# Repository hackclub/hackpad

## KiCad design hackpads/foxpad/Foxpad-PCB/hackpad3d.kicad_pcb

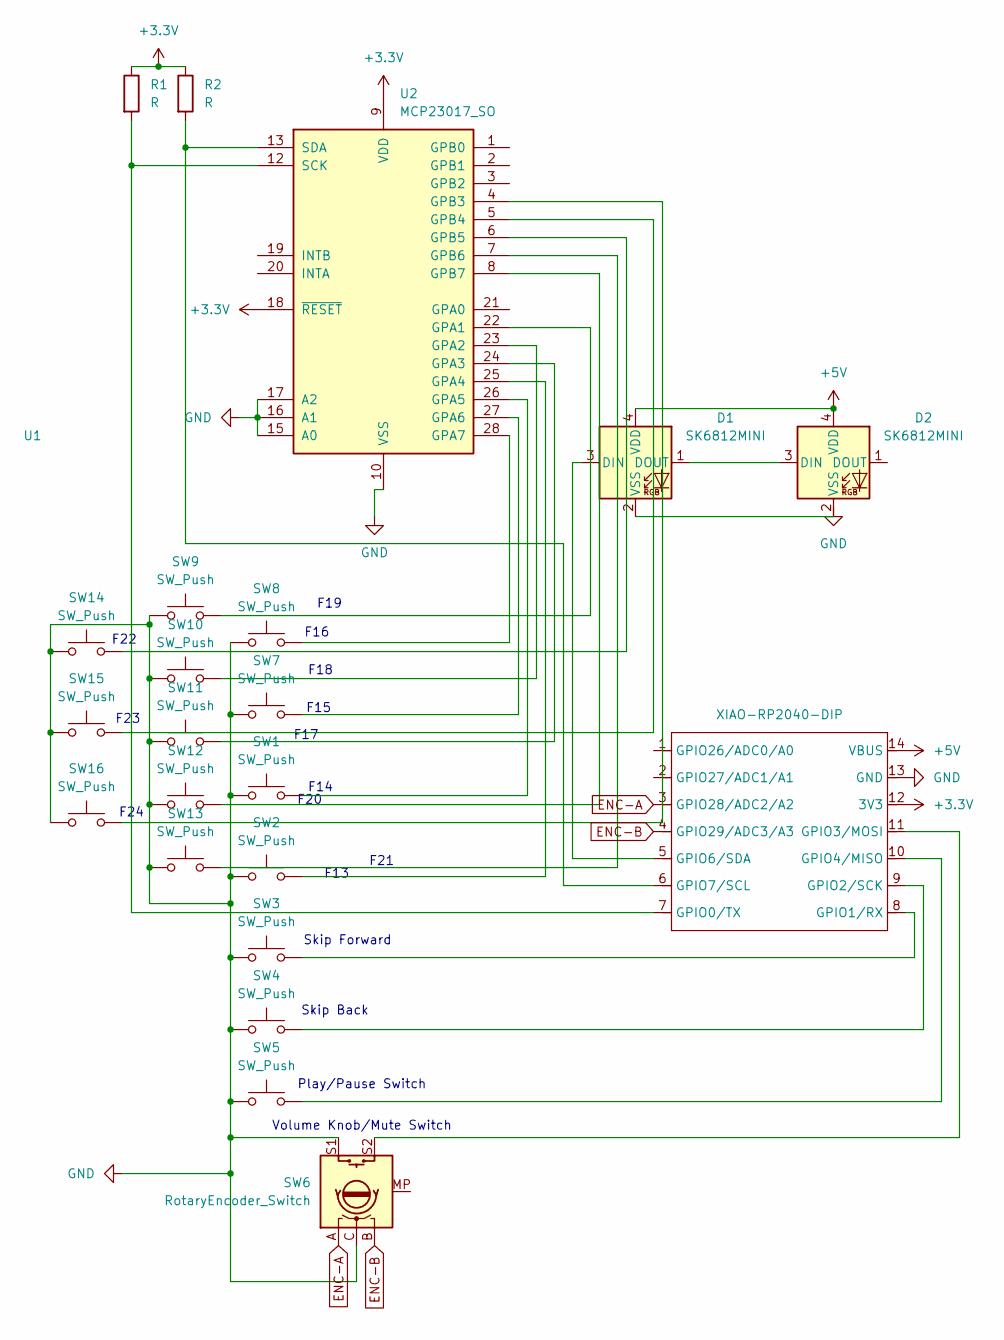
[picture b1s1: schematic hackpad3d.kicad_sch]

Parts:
D1, D2: SK6812MINI; LED_SK6812MINI_PLCC4_3.5x3.5mm_P1.75mm_3D
R1, R2: R; R_Axial_DIN0204_L3.6mm_D1.6mm_P7.62mm_Horizontal
SW1, SW2, SW3, SW4, SW5, SW7, SW8, SW9, SW10, SW11, SW12, SW13, SW14, SW15, SW16: SW_Push; SW_Cherry_MX_1.00u_PCB_3D
SW6: RotaryEncoder_Switch; RotaryEncoder_Alps_EC11E-Switch_Vertical_H20mm_CircularMoun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
U1: XIAO-RP2040-DIP; XIAO-RP2040-DIP-3D
U2: MCP23017_SO; SOIC-28W_7.5x17.9mm_P1.27mm

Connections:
+3.3V: R1.1, R2.1, U1.12 (3V3), U2.9 (VDD), U2.18 (~RESET)
+5V: D1.4 (VDD), D2.4 (VDD), U1.14 (VBUS)
ENC-A: SW6.A, U1.3 (GPIO28/ADC2/A2)
ENC-B: SW6.B, U1.4 (GPIO29/ADC3/A3)
GND: SW1.1, SW2.1, SW3.1, SW4.1, SW5.1, SW6.C, SW6.S1, SW7.1, SW8.1, SW9.1, SW10.1, SW11.1, SW12.1, SW13.1, SW14.1, SW15.1, SW16.1, U1.13 (GND), U2.10 (VSS), U2.15 (A0), U2.16 (A1), U2.17 (A2)
unnamed: D1.3 (DIN), U1.5 (GPIO6/SDA)
unnamed: D1.1 (DOUT), D2.3 (DIN)
unnamed: D1.2 (VSS), D2.2 (VSS)
unnamed: R1.2, U1.7 (GPIO0/TX), U2.12 (SCK)
unnamed: SW3.2, U1.8 (GPIO1/RX)
unnamed: SW4.2, U1.9 (GPIO2/SCK)
unnamed: SW6.S2, U1.11 (GPIO3/MOSI)
unnamed: SW5.2, U1.10 (GPIO4/MISO)
unnamed: R2.2, U1.6 (GPIO7/SCL), U2.13 (SDA)
unnamed: SW9.2, U2.22 (GPA1)
unnamed: SW10.2, U2.23 (GPA2)
unnamed: SW11.2, U2.24 (GPA3)
unnamed: SW2.2, U2.25 (GPA4)
unnamed: SW1.2, U2.26 (GPA5)
unnamed: SW7.2, U2.27 (GPA6)
unnamed: SW8.2, U2.28 (GPA7)
unnamed: SW16.2, U2.4 (GPB3)
unnamed: SW15.2, U2.5 (GPB4)
unnamed: SW14.2, U2.6 (GPB5)
unnamed: SW13.2, U2.7 (GPB6)
unnamed: SW12.2, U2.8 (GPB7)

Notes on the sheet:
F16
F18
F13
F17
F23
Volume Knob/Mute Switch
F19
Skip Forward
F20
F22
F24
F15
Skip Back
F21
Play/Pause Switch
F14

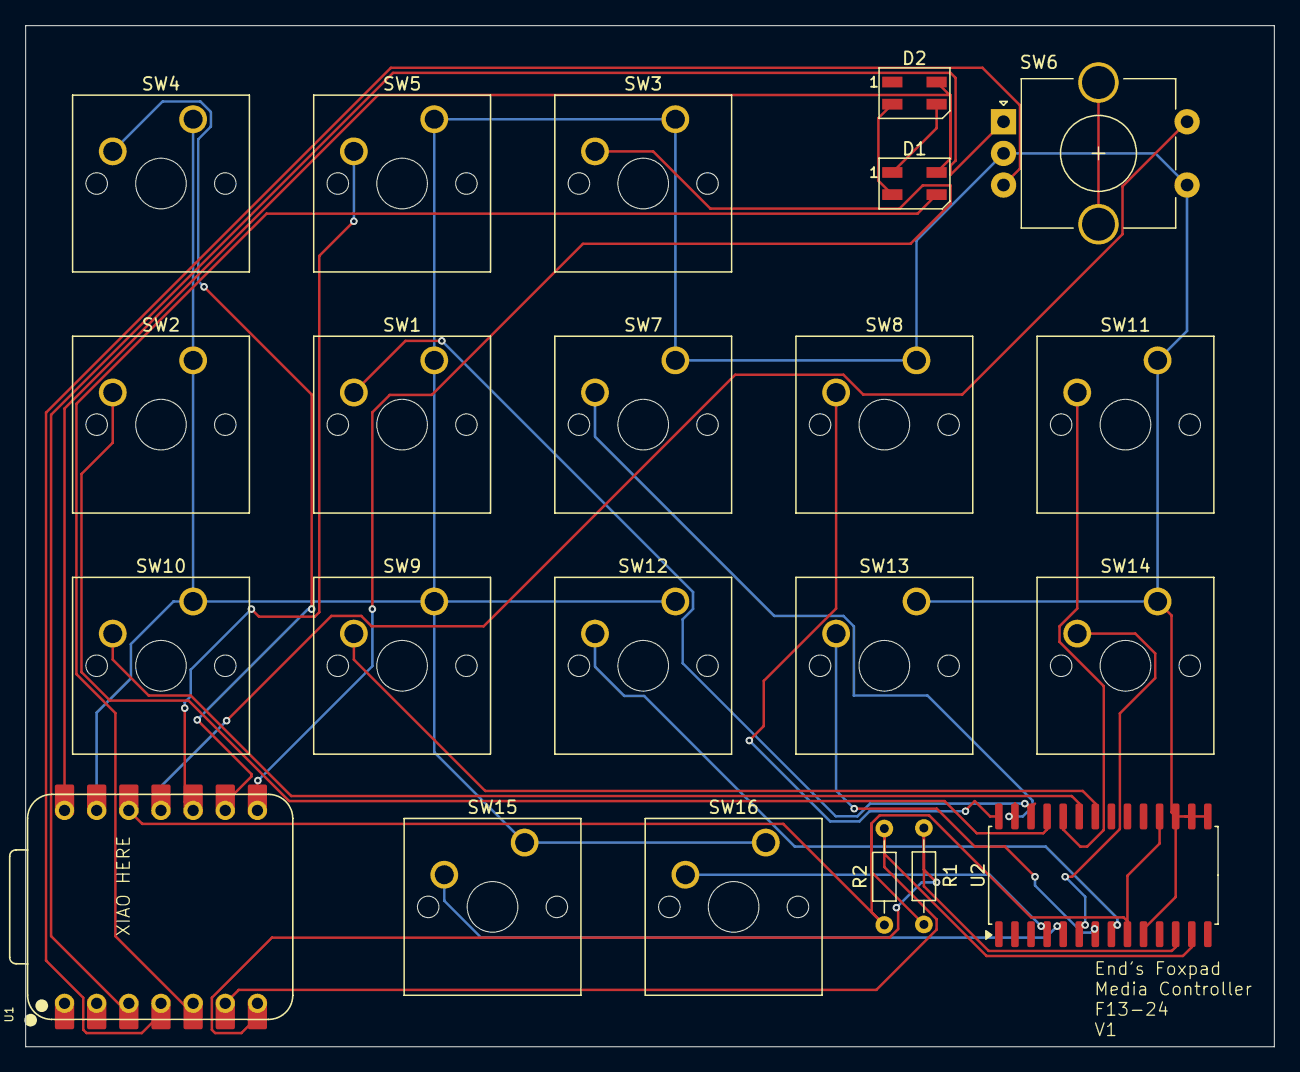
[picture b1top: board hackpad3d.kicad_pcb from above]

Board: 2 copper layers, 98.7 x 80.7 mm, 22 parts (0 on the bottom side), 26 nets.

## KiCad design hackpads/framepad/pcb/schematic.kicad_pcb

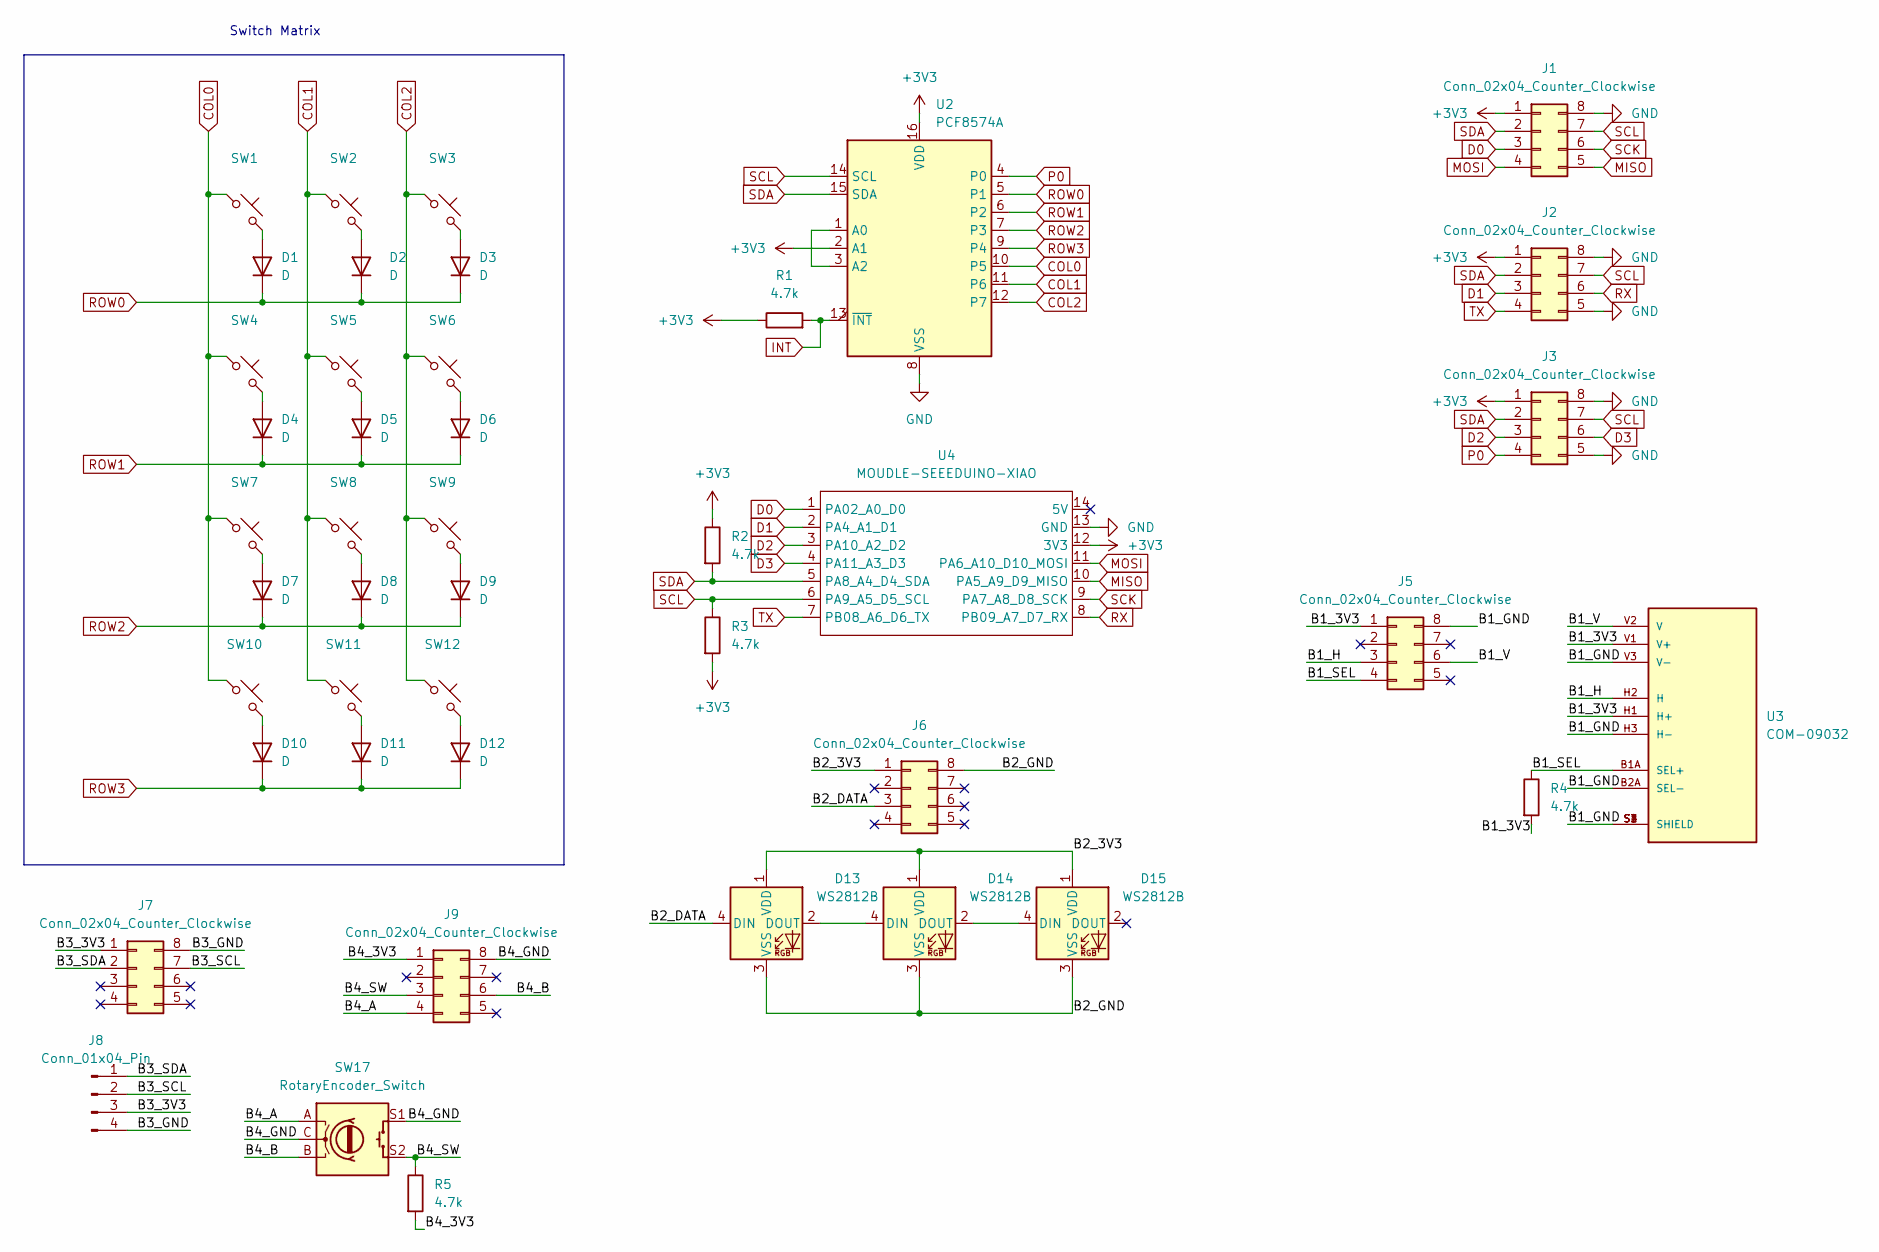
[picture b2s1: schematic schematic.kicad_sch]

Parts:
D1, D2, D3, D4, D5, D6, D7, D8, D9, D10, D11, D12: D; D_DO-35_SOD27_P7.62mm_Horizontal
D13, D14, D15: WS2812B; LED_WS2812B_PLCC4_5.0x5.0mm_P3.2mm
J1, J2, J3: Conn_02x04_Counter_Clockwise; PinHeader_2x04_P2.54mm_Horizontal
J5, J6, J7, J9: Conn_02x04_Counter_Clockwise; PinSocket_2x04_P2.54mm_Horizontal
J8: Conn_01x04_Pin; PinHeader_1x04_P2.54mm_Vertical
R1, R2, R3, R4, R5: 4.7k; R_Axial_DIN0207_L6.3mm_D2.5mm_P10.16mm_Horizontal
SW1, SW2, SW3, SW4, SW5, SW6, SW7, SW8, SW9, SW10, SW11, SW12: SW_Push_45deg; SW_Cherry_MX_1.00u_PCB
SW17: RotaryEncoder_Switch; RotaryEncoder_Alps_EC11E-Switch_Vertical_H20mm
U2: PCF8574A; N16
U3: COM-09032; XDCR_COM-09032; PARTREV N/A
U4: MOUDLE-SEEEDUINO-XIAO; XIAO-Generic-Hybrid-14P-2.54-21X17.8MM

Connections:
+3V3: J1.1, J2.1, J3.1, R1.1, R2.1, R3.2, U2.2 (A1), U2.16 (VDD), U4.12 (3V3)
/B2_3V3: D13.1 (VDD), D14.1 (VDD), D15.1 (VDD), J6.1
/B2_DATA: D13.4 (DIN), J6.3
/B2_GND: D13.3 (VSS), D14.3 (VSS), D15.3 (VSS), J6.8
/B3_3V3: J7.1, J8.3
/B3_GND: J7.8, J8.4
/B3_SCL: J7.7, J8.2
/B3_SDA: J7.2, J8.1
/B4_3V3: J9.1, R5.2
/B4_A: J9.4, SW17.A
/B4_B: J9.6, SW17.B
/B4_GND: J9.8, SW17.C, SW17.S1
/B4_SW: J9.3, R5.1, SW17.S2
COL0: SW1.1, SW4.1, SW7.1, SW10.1, U2.10 (P5)
COL1: SW2.1, SW5.1, SW8.1, SW11.1, U2.11 (P6)
COL2: SW3.1, SW6.1, SW9.1, SW12.1, U2.12 (P7)
D0: J1.3, U4.1 (PA02_A0_D0)
D1: J2.3, U4.2 (PA4_A1_D1)
D2: J3.3, U4.3 (PA10_A2_D2)
D3: J3.6, U4.4 (PA11_A3_D3)
GND: J1.8, J2.5, J2.8, J3.5, J3.8, U2.8 (VSS), U4.13 (GND)
INT: R1.2, U2.13 (~INT)
MISO: J1.5, U4.10 (PA5_A9_D9_MISO)
MOSI: J1.4, U4.11 (PA6_A10_D10_MOSI)
unnamed: D1.2 (A), SW1.2
unnamed: D2.2 (A), SW2.2
unnamed: D3.2 (A), SW3.2
unnamed: D4.2 (A), SW4.2
unnamed: D5.2 (A), SW5.2
unnamed: D6.2 (A), SW6.2
unnamed: D7.2 (A), SW7.2
unnamed: D8.2 (A), SW8.2
unnamed: D9.2 (A), SW9.2
unnamed: D10.2 (A), SW10.2
unnamed: D11.2 (A), SW11.2
unnamed: D12.2 (A), SW12.2
unnamed: D13.2 (DOUT), D14.4 (DIN)
unnamed: D14.2 (DOUT), D15.4 (DIN)
unnamed: J5.1, R4.2, U3.H1 (H+), U3.V1 (V+)
unnamed: J5.3, U3.H2 (H)
unnamed: J5.4, R4.1, U3.B1A (SEL+)
unnamed: J5.6, U3.V2 (V)
unnamed: J5.8, U3.B2A (SEL-), U3.H3 (H-), U3.S1 (SHIELD), U3.S2 (SHIELD), U3.S3 (SHIELD), U3.S4 (SHIELD), U3.V3 (V-)
unnamed: U2.1 (A0), U2.3 (A2)
P0: J3.4, U2.4 (P0)
ROW0: D1.1 (K), D2.1 (K), D3.1 (K), U2.5 (P1)
ROW1: D4.1 (K), D5.1 (K), D6.1 (K), U2.6 (P2)
ROW2: D7.1 (K), D8.1 (K), D9.1 (K), U2.7 (P3)
ROW3: D10.1 (K), D11.1 (K), D12.1 (K), U2.9 (P4)
RX: J2.6, U4.8 (PB09_A7_D7_RX)
SCK: J1.6, U4.9 (PA7_A8_D8_SCK)
SCL: J1.7, J2.7, J3.7, R3.1, U2.14 (SCL), U4.6 (PA9_A5_D5_SCL)
SDA: J1.2, J2.2, J3.2, R2.2, U2.15 (SDA), U4.5 (PA8_A4_D4_SDA)
TX: J2.4, U4.7 (PB08_A6_D6_TX)

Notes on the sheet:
Switch Matrix

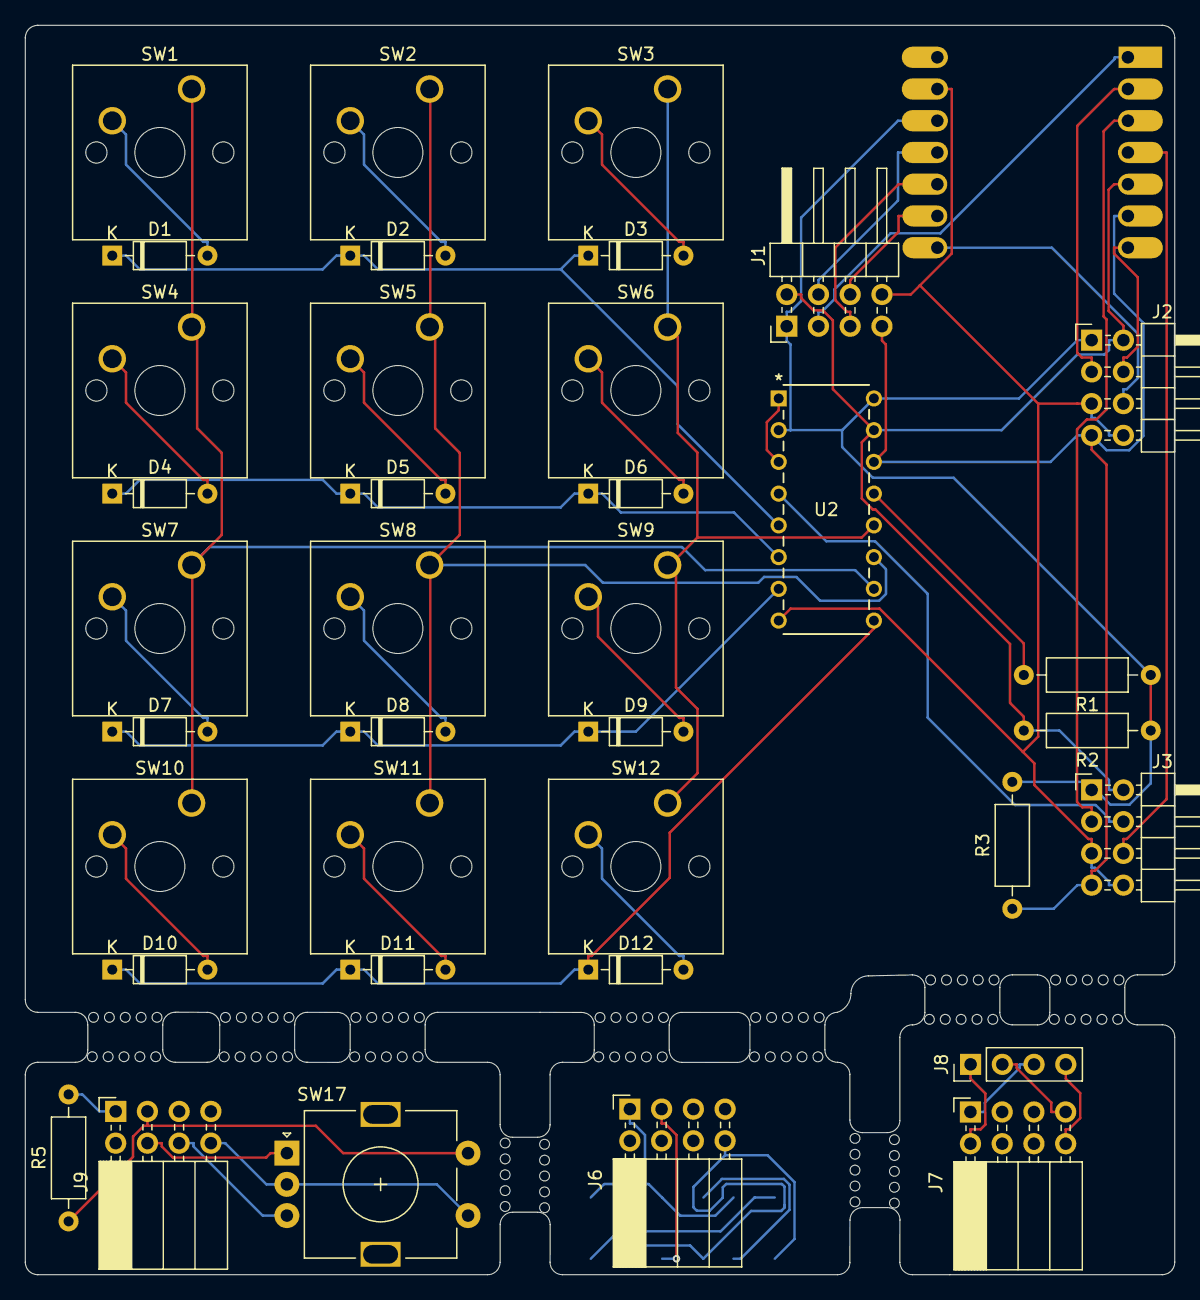
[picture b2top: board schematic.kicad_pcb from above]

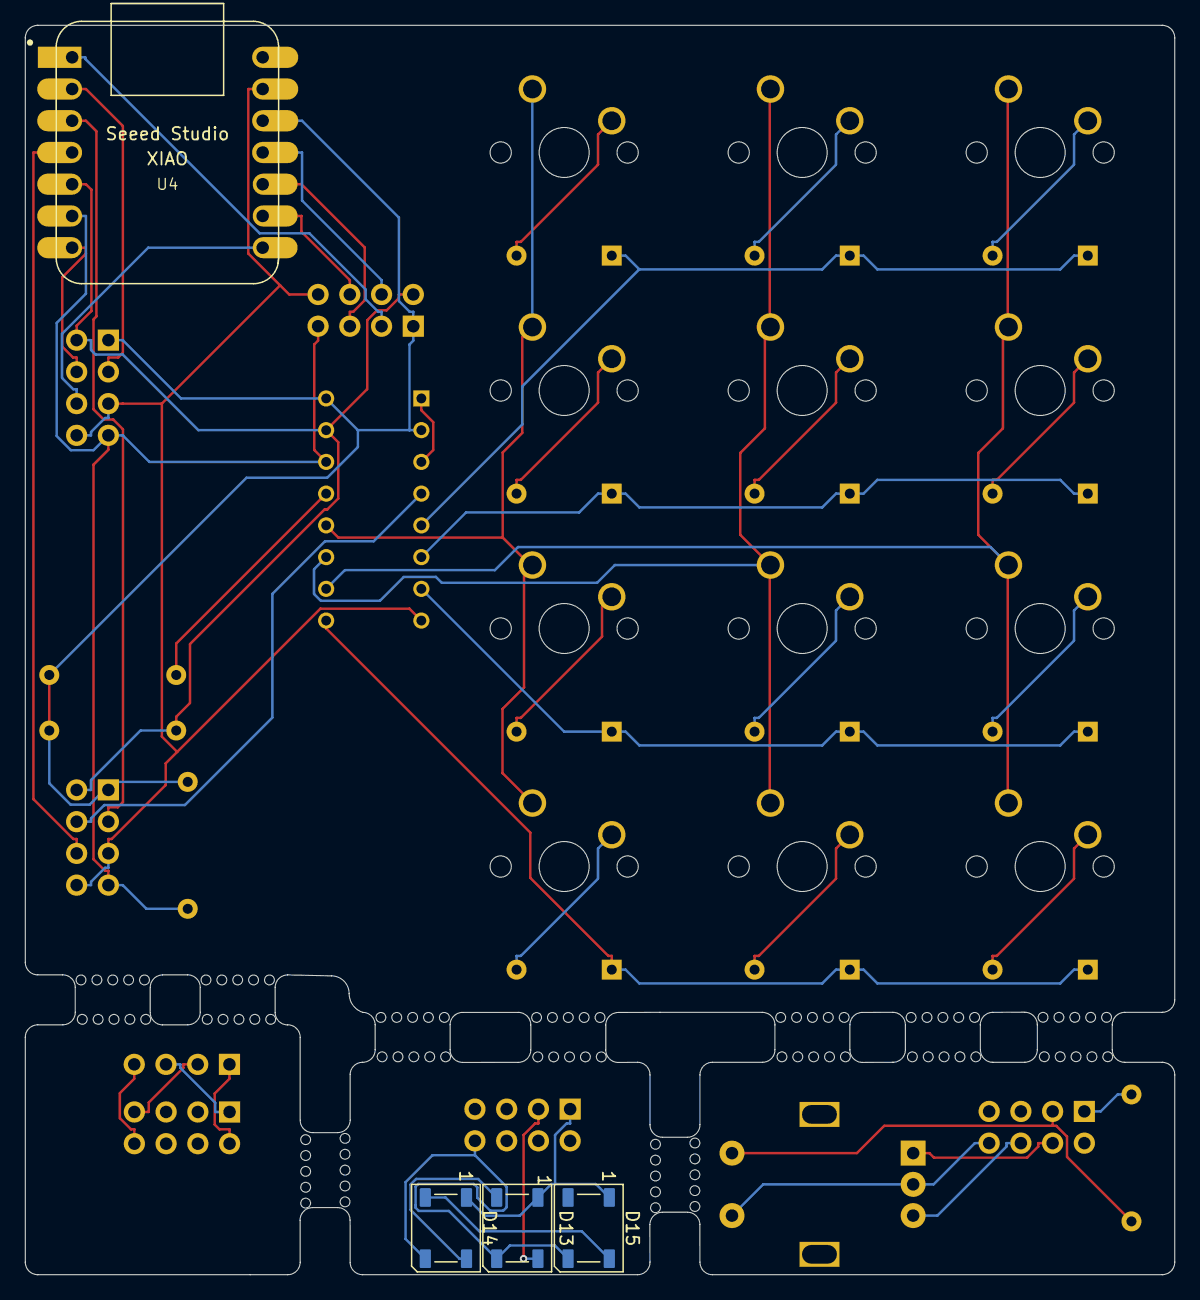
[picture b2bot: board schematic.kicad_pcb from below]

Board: 2 copper layers, 92.0 x 100.0 mm, 59 parts (4 on the bottom side), 49 nets.

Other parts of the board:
B00, B01, B10, B11, B20, B21, B30, B31, B40, B41, B50, B51, B60, B61, B70, B71, B80, B81: breakaway-mousebites

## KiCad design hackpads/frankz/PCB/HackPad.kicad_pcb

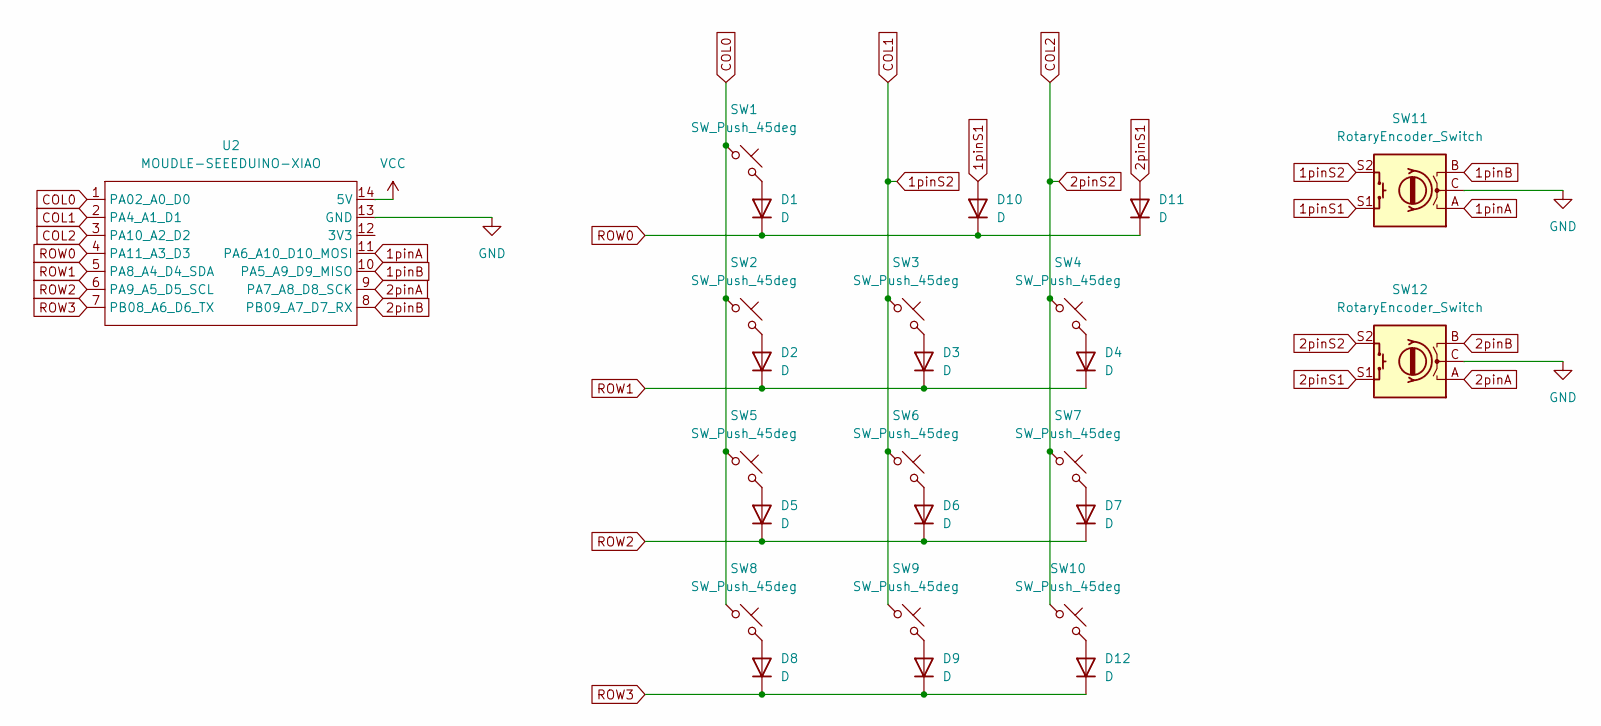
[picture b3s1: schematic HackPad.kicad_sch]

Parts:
D1, D2, D3, D4, D5, D6, D7, D8, D9, D10, D11, D12: D; Diode_DO-35
SW1, SW2, SW3, SW4, SW5, SW6, SW7, SW8, SW9, SW10: SW_Push_45deg; MX_PCB_1.00u
SW11, SW12: RotaryEncoder_Switch; Encoder_EC11_MX
U2: MOUDLE-SEEEDUINO-XIAO; Seeed_XIAO_RP2040

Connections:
1pinA: SW11.A, U2.11 (PA6_A10_D10_MOSI)
1pinB: SW11.B, U2.10 (PA5_A9_D9_MISO)
1pinS1: D10.2 (A), SW11.S1
1pinS2: SW3.1, SW6.1, SW9.1, SW11.S2, U2.2 (PA4_A1_D1)
2pinA: SW12.A, U2.9 (PA7_A8_D8_SCK)
2pinB: SW12.B, U2.8 (PB09_A7_D7_RX)
2pinS1: D11.2 (A), SW12.S1
2pinS2: SW4.1, SW7.1, SW10.1, SW12.S2, U2.3 (PA10_A2_D2)
COL0: SW1.1, SW2.1, SW5.1, SW8.1, U2.1 (PA02_A0_D0)
GND: SW11.C, SW12.C, U2.13 (GND)
unnamed: D1.2 (A), SW1.2
unnamed: D2.2 (A), SW2.2
unnamed: D3.2 (A), SW3.2
unnamed: D4.2 (A), SW4.2
unnamed: D5.2 (A), SW5.2
unnamed: D6.2 (A), SW6.2
unnamed: D7.2 (A), SW7.2
unnamed: D8.2 (A), SW8.2
unnamed: D9.2 (A), SW9.2
unnamed: D12.2 (A), SW10.2
ROW0: D1.1 (K), D10.1 (K), D11.1 (K), U2.4 (PA11_A3_D3)
ROW1: D2.1 (K), D3.1 (K), D4.1 (K), U2.5 (PA8_A4_D4_SDA)
ROW2: D5.1 (K), D6.1 (K), D7.1 (K), U2.6 (PA9_A5_D5_SCL)
ROW3: D8.1 (K), D9.1 (K), D12.1 (K), U2.7 (PB08_A6_D6_TX)
VCC: U2.14 (5V)

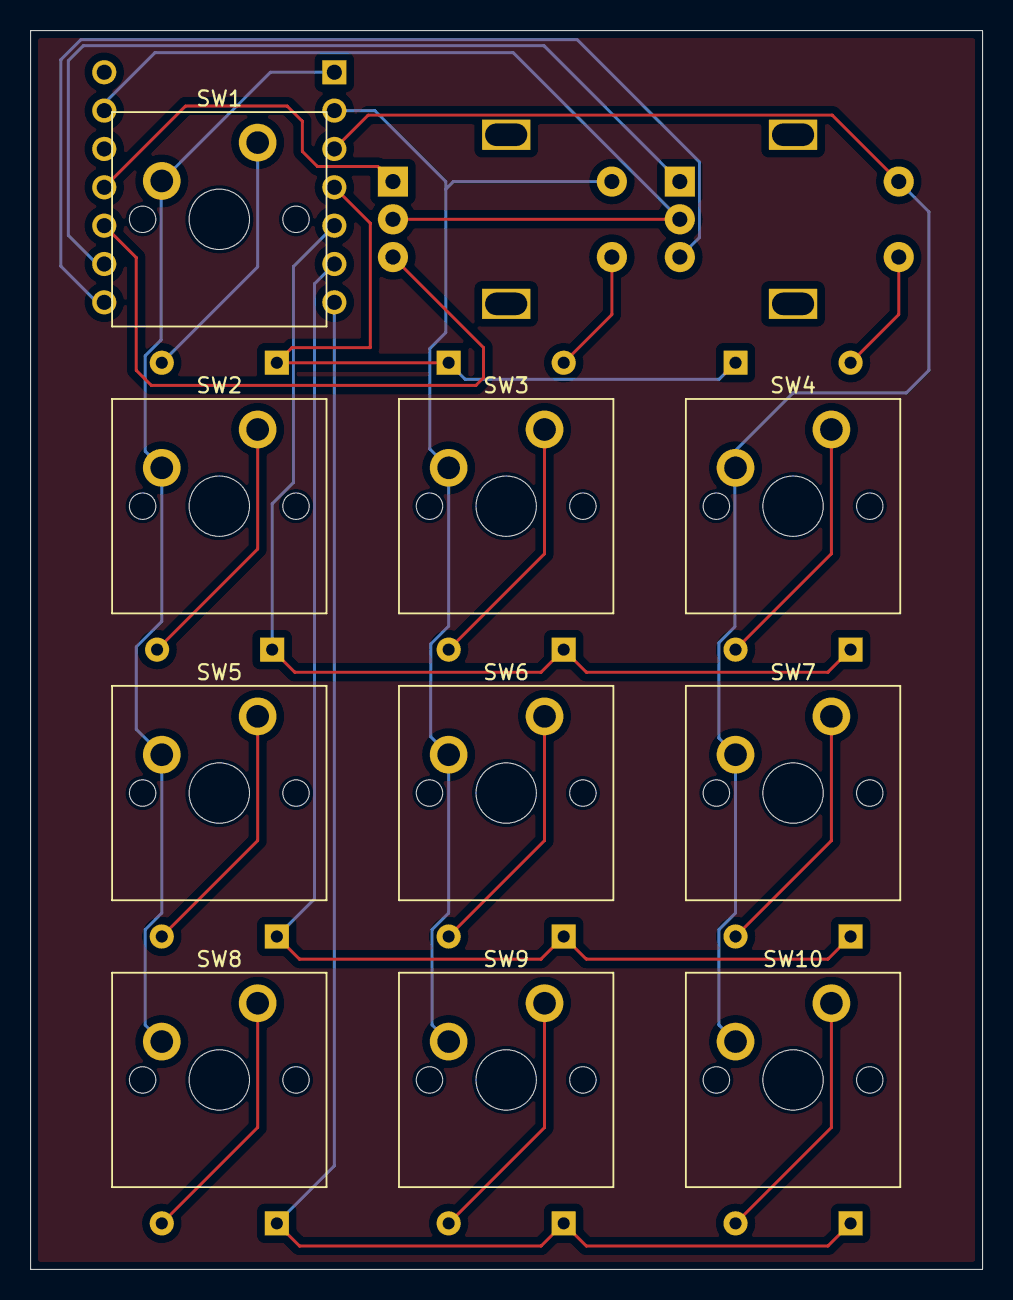
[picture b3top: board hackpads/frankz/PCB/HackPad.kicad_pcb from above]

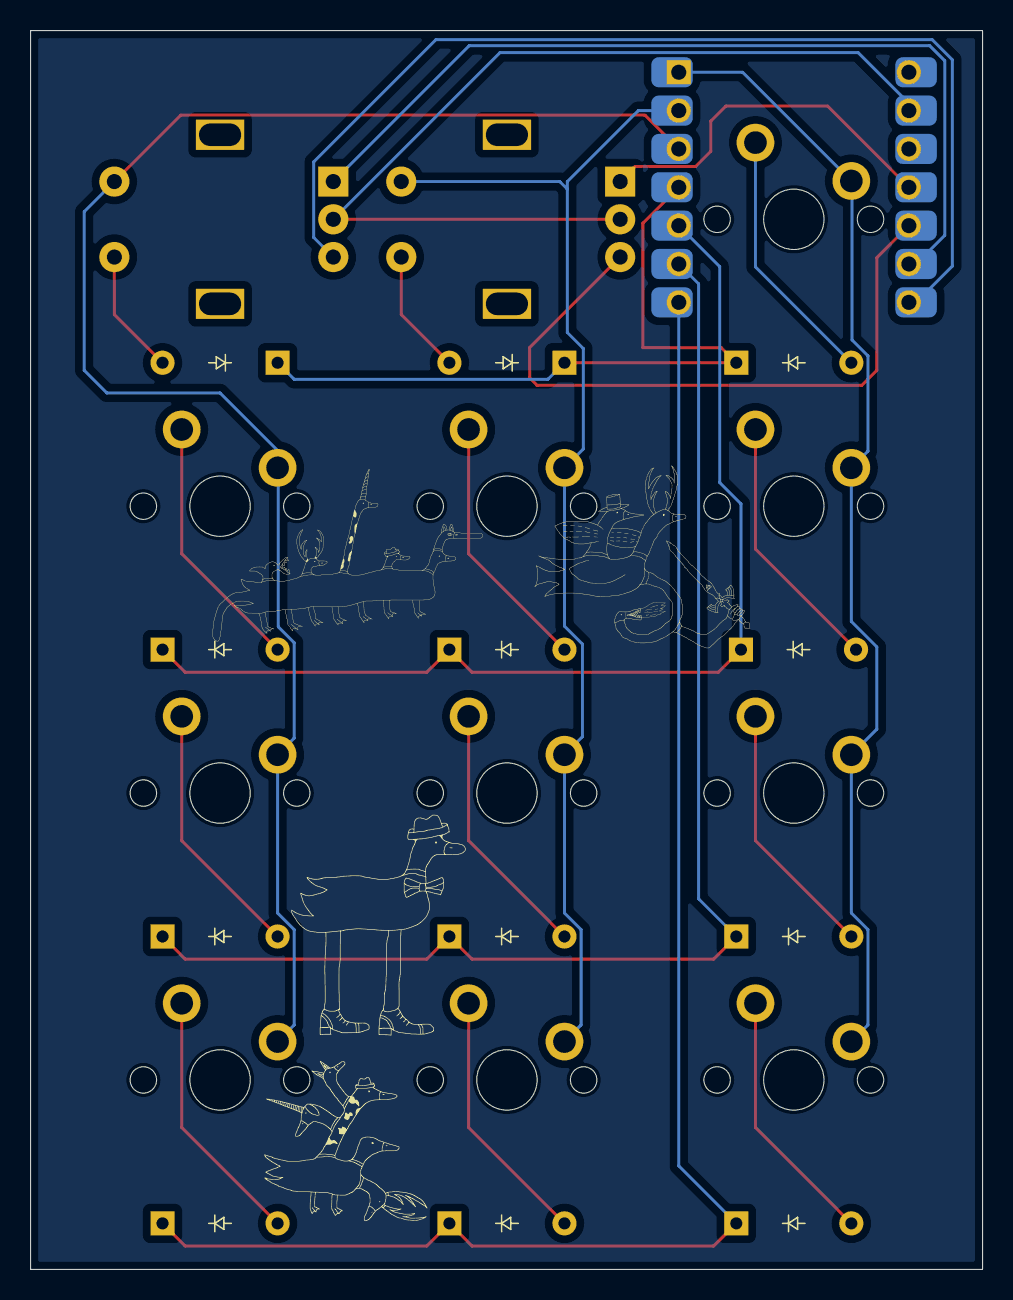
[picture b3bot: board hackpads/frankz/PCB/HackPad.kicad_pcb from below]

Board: 2 copper layers, 63.0 x 82.0 mm, 25 parts (13 on the bottom side), 24 nets.

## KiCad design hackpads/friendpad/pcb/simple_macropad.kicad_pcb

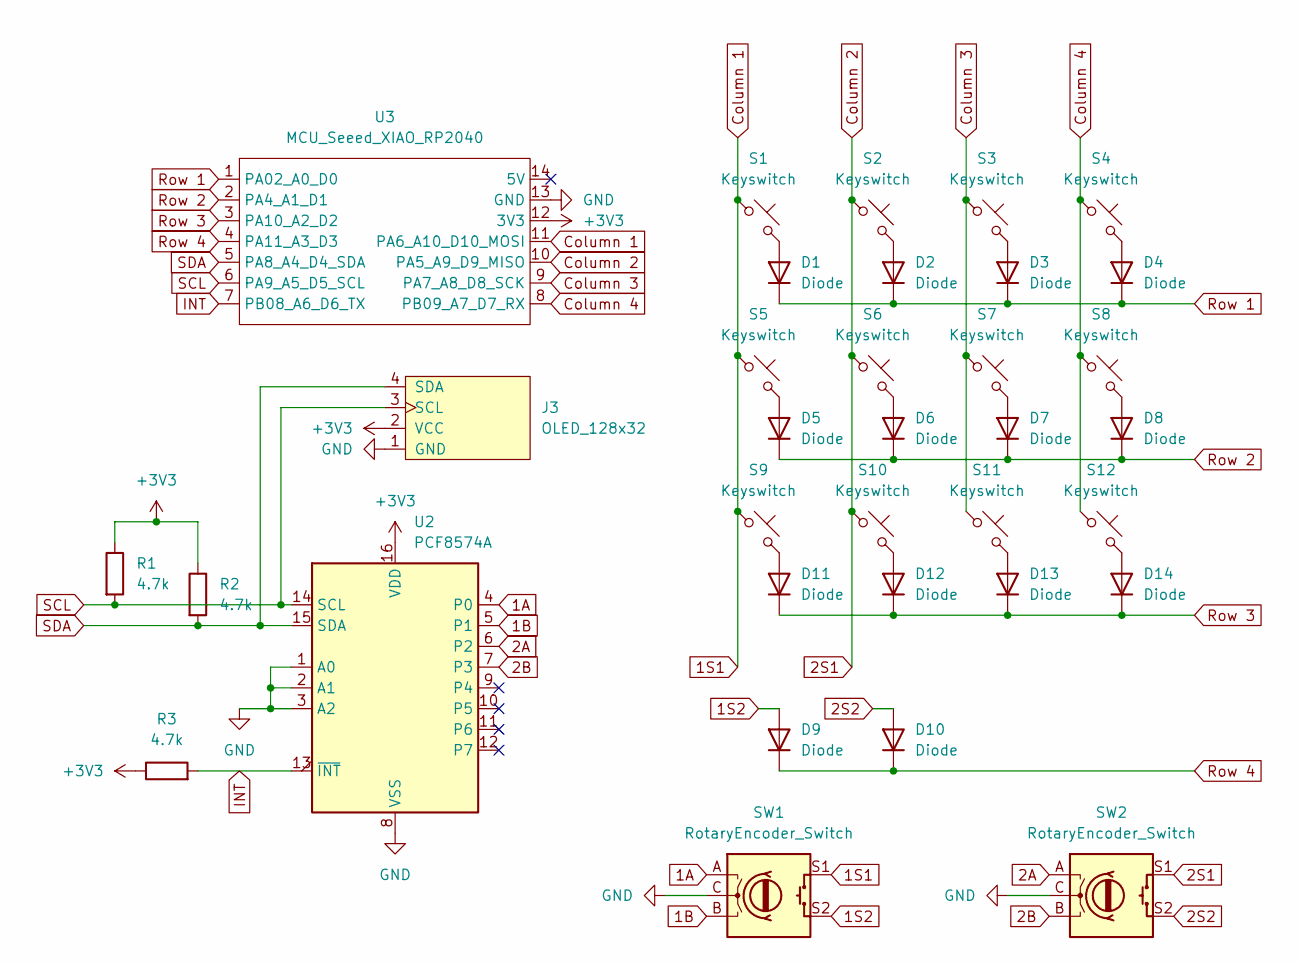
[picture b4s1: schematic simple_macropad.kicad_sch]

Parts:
D1, D2, D3, D4, D5, D6, D7, D8, D9, D10, D11, D12, D13, D14: Diode; Diode_DO-35
J3: OLED_128x32
R1, R2, R3: 4.7k; R_Axial_DIN0207_L6.3mm_D2.5mm_P10.16mm_Horizontal
S1, S2, S3, S4, S5, S6, S7, S8, S9, S10, S11, S12: Keyswitch; MX_PCB_1.00u
SW1, SW2: RotaryEncoder_Switch; RotaryEncoder_Alps_EC11E-Switch_Vertical_H20mm
U2: PCF8574A; DIP-16_W7.62mm
U3: MCU_Seeed_XIAO_RP2040; Seeed_XIAO_RP2040

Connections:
1A: SW1.A, U2.4 (P0)
1B: SW1.B, U2.5 (P1)
1S1: S1.1, S5.1, S9.1, SW1.S1, U3.11 (PA6_A10_D10_MOSI)
1S2: D9.2 (A), SW1.S2
2A: SW2.A, U2.6 (P2)
2B: SW2.B, U2.7 (P3)
2S1: S2.1, S6.1, S10.1, SW2.S1, U3.10 (PA5_A9_D9_MISO)
2S2: D10.2 (A), SW2.S2
+3V3: J3.2 (VCC), R1.1, R2.1, R3.1, U2.16 (VDD), U3.12 (3V3)
Column 3: S3.1, S7.1, S11.1, U3.9 (PA7_A8_D8_SCK)
Column 4: S4.1, S8.1, S12.1, U3.8 (PB09_A7_D7_RX)
GND: J3.1 (GND), SW1.C, SW2.C, U2.1 (A0), U2.2 (A1), U2.3 (A2), U2.8 (VSS), U3.13 (GND)
INT: R3.2, U2.13 (~INT), U3.7 (PB08_A6_D6_TX)
unnamed: D1.2 (A), S1.2
unnamed: D2.2 (A), S2.2
unnamed: D3.2 (A), S3.2
unnamed: D4.2 (A), S4.2
unnamed: D5.2 (A), S5.2
unnamed: D6.2 (A), S6.2
unnamed: D7.2 (A), S7.2
unnamed: D8.2 (A), S8.2
unnamed: D11.2 (A), S9.2
unnamed: D12.2 (A), S10.2
unnamed: D13.2 (A), S11.2
unnamed: D14.2 (A), S12.2
Row 1: D1.1 (K), D2.1 (K), D3.1 (K), D4.1 (K), U3.1 (PA02_A0_D0)
Row 2: D5.1 (K), D6.1 (K), D7.1 (K), D8.1 (K), U3.2 (PA4_A1_D1)
Row 3: D11.1 (K), D12.1 (K), D13.1 (K), D14.1 (K), U3.3 (PA10_A2_D2)
Row 4: D9.1 (K), D10.1 (K), U3.4 (PA11_A3_D3)
SCL: J3.3 (SCL), R1.2, U2.14 (SCL), U3.6 (PA9_A5_D5_SCL)
SDA: J3.4 (SDA), R2.2, U2.15 (SDA), U3.5 (PA8_A4_D4_SDA)

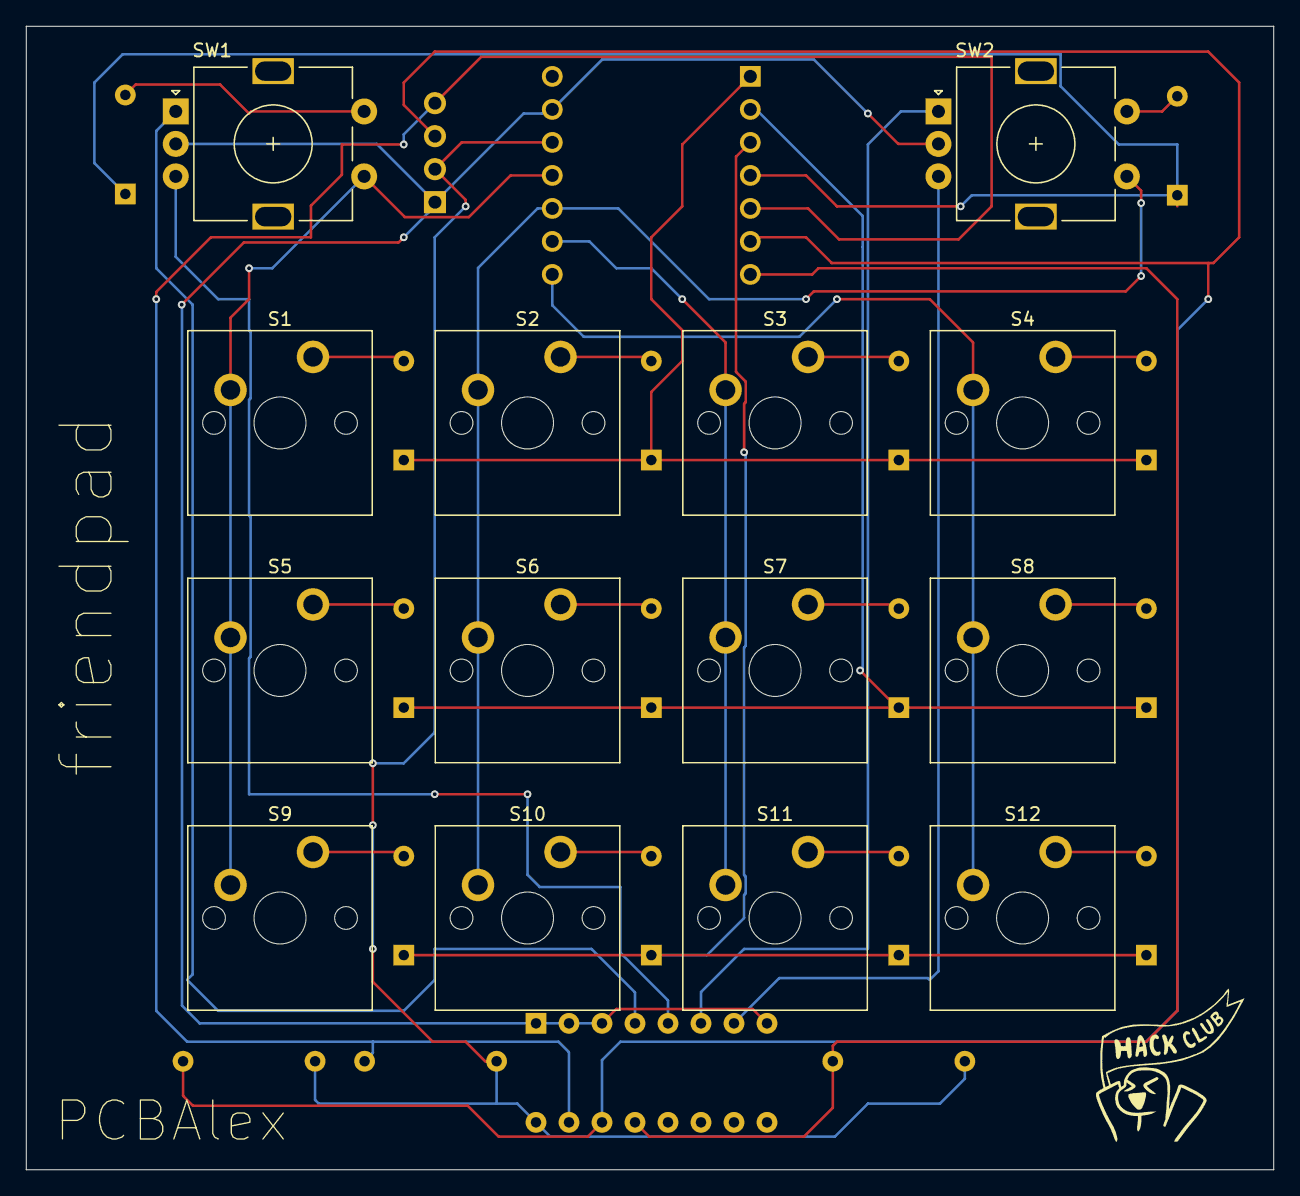
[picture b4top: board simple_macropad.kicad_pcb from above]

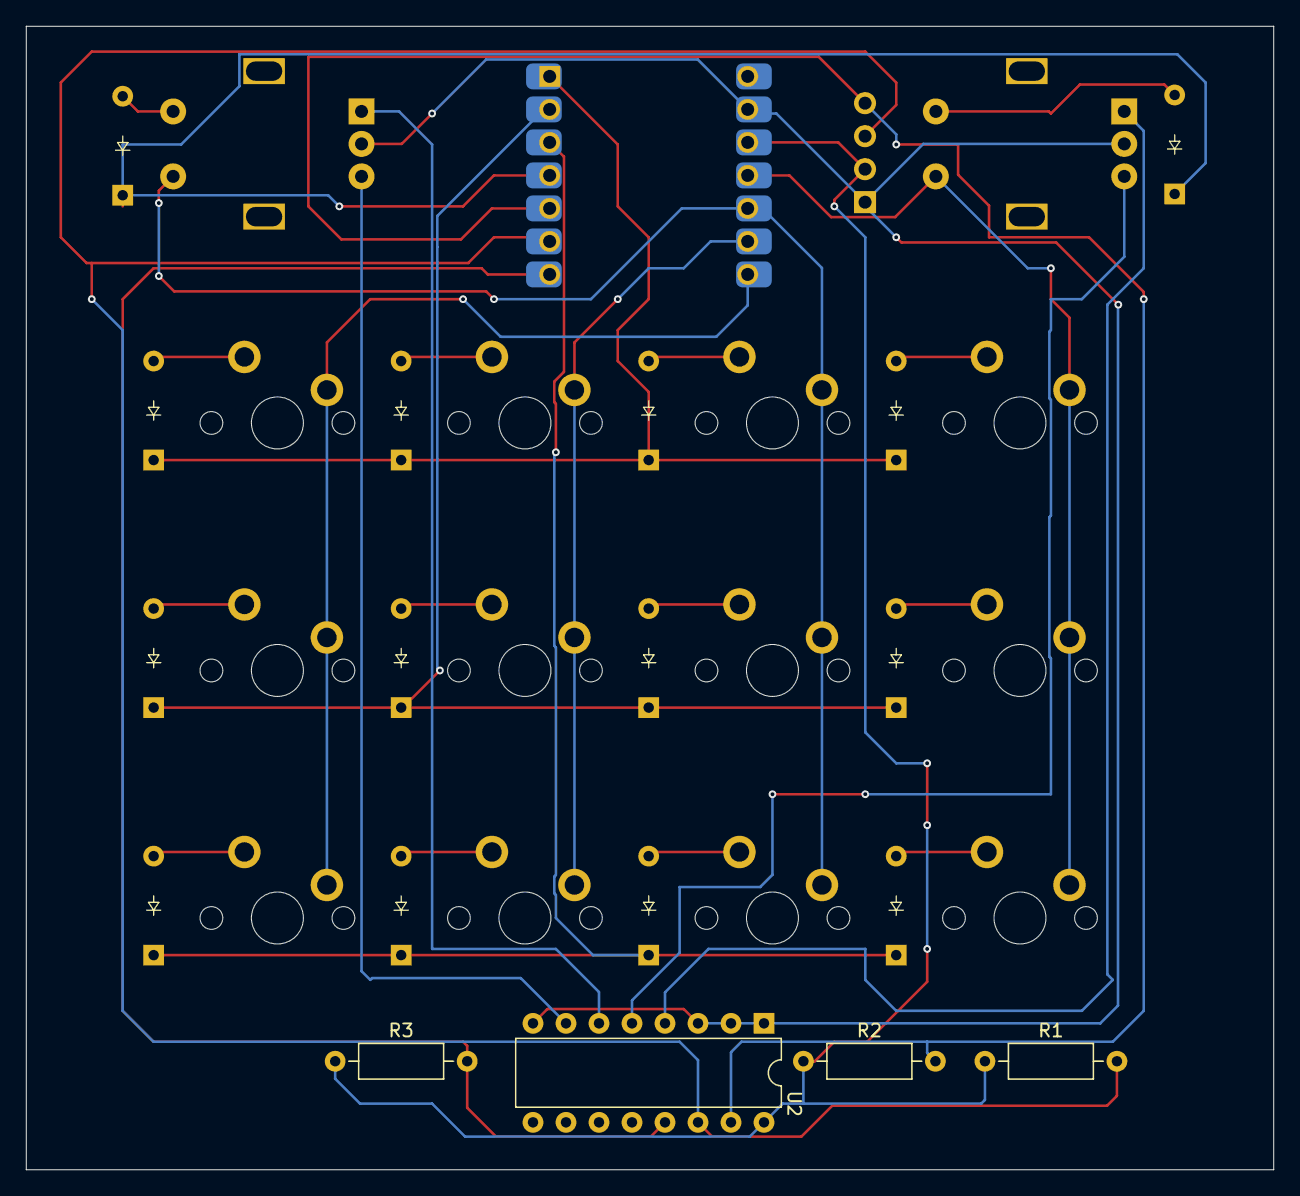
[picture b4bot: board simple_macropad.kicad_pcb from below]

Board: 2 copper layers, 96.0 x 88.0 mm, 35 parts (19 on the bottom side), 31 nets.

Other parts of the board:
 : LOGO

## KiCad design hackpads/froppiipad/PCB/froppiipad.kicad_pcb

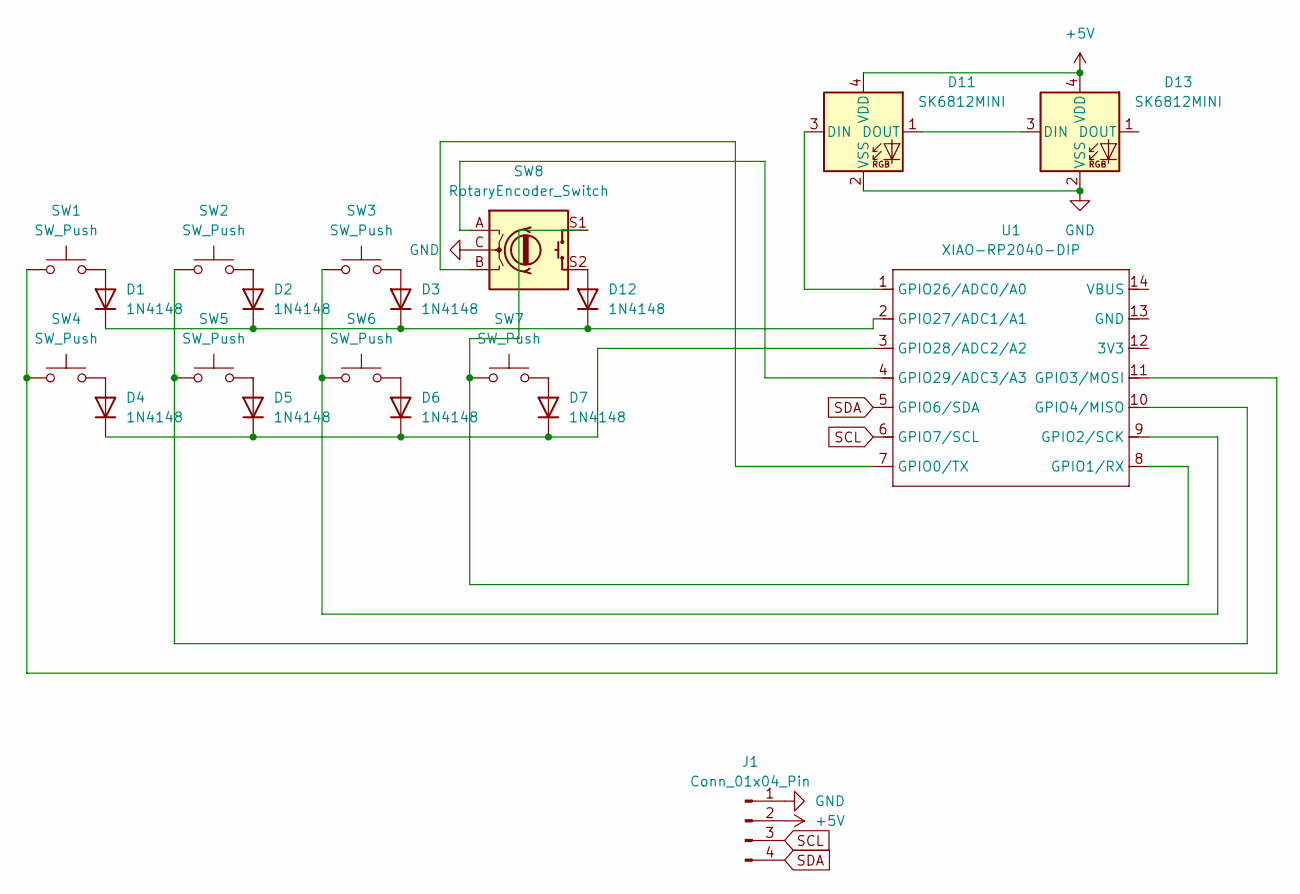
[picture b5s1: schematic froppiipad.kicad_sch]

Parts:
D1, D2, D3, D4, D5, D6, D7, D12: 1N4148; D_DO-35_SOD27_P7.62mm_Horizontal
D11, D13: SK6812MINI; LED_SK6812MINI_PLCC4_3.5x3.5mm_P1.75mm
J1: Conn_01x04_Pin; SSD1306-0.91-OLED-4pin-128x32
SW1, SW2, SW3, SW4, SW5, SW6, SW7: SW_Push; SW_Cherry_MX_1.00u_PCB
SW8: RotaryEncoder_Switch; RotaryEncoder_Alps_EC11E-Switch_Vertical_H20mm
U1: XIAO-RP2040-DIP

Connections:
+5V: D11.4 (VDD), D13.4 (VDD), J1.2
GND: D11.2 (VSS), D13.2 (VSS), J1.1, SW8.C
unnamed: D1.2 (A), SW1.2
unnamed: D1.1 (K), D2.1 (K), D3.1 (K), D12.1 (K), U1.2 (GPIO27/ADC1/A1)
unnamed: D2.2 (A), SW2.2
unnamed: D3.2 (A), SW3.2
unnamed: D4.2 (A), SW4.2
unnamed: D4.1 (K), D5.1 (K), D6.1 (K), D7.1 (K), U1.3 (GPIO28/ADC2/A2)
unnamed: D5.2 (A), SW5.2
unnamed: D6.2 (A), SW6.2
unnamed: D7.2 (A), SW7.2
unnamed: D11.3 (DIN), U1.1 (GPIO26/ADC0/A0)
unnamed: D11.1 (DOUT), D13.3 (DIN)
unnamed: D12.2 (A), SW8.S2
unnamed: SW8.B, U1.7 (GPIO0/TX)
unnamed: SW7.1, SW8.S1, U1.8 (GPIO1/RX)
unnamed: SW3.1, SW6.1, U1.9 (GPIO2/SCK)
unnamed: SW1.1, SW4.1, U1.11 (GPIO3/MOSI)
unnamed: SW2.1, SW5.1, U1.10 (GPIO4/MISO)
unnamed: SW8.A, U1.4 (GPIO29/ADC3/A3)
SCL: J1.3, U1.6 (GPIO7/SCL)
SDA: J1.4, U1.5 (GPIO6/SDA)
